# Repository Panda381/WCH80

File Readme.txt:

WCH80 BabyPC - mini-computer with CH32V002, ZX80 clone
======================================================
Version 1.0, September 2025

Copyright (c) 2025 Miroslav Nemecek

Panda38@seznam.cz
hardyplotter2@gmail.com
https://github.com/Panda381/WCH80
https://www.breatharian.eu/hw/wch80/index_en.html

This project is part of the CH32LibSDK library:
https://github.com/Panda381/CH32LibSDK
https://www.breatharian.eu/hw/ch32libsdk/index_en.html

License
-------
All of my software creations are distributed under the Unlicense
https://spdx.org/licenses/Unlicense.html,
and my hardware creations under the CC0 license
https://creativecommons.org/publicdomain/zero/1.0/legalcode.en.
You are free to use, modify, and distribute them for any purpose without having
to credit me as the author. The exception is content derived from third-party
sources. These third-party components are not covered by my Unlicense or CC0
licenses, but rather by the original license terms of their authors. These
components are marked in the code, and when using them, you must comply with
the terms of the original licenses.

Folders
-------
!Babypc ... binaries - firmware of CPU1 and CPU2, BASIC80, games
_devices ... source codes of WCH80 device library
Babypc ... source codes of firmware of CPU1 and CPU2, BASIC80, games

Description
-----------
The WCH80 BabyPC is an inexpensive mini-computer with two CH32V002
processors, created based on the ZX80 computer. It is not an emulator;
the computer does not emulate the ZX80 computer's ROM, nor does it emulate Z80
machine instructions. It was created as a completely independent computer with
the BASIC80 programming language and VGA monitor output, only replicating the
ZX80's functionality as closely as possible. It uses a CH32V002A4M6 processor,
which, thanks to its large 1.27 mm pin pitch, is suitable for easy soldering
even for novice designers. Together with other THT components, the WCH80 is
particularly suitable as a kit for novice designers. The built-in BASIC80
programming language is used to familiarize users with computer programming and
to try out how programmers programmed in the 1980s.

The computer does not contain a storage medium for saving programs. Your own
programs can be saved directly to the processor's flash memory. There are 14
memory slots available, i.e. 14 places to store your own programs, numbered 0
to 13. Slot 0 is located in the main CPU1 processor. When stored in slot 0,
data variables are also stored along with the program (more precisely, only the
first half of the memory with variables). Slot 0 is automatically loaded into
the program memory when the computer is turned on. Memory slots 1 to 13 are
located in the second processor, CPU2. All slots allow the entire memory with
the program to be stored, except for the last slot 13, which is only half the
size.

After initial programming, the processors contain 28 sample programs and games
written in BASIC80. Once the processors have been programmed, the programmer is
no longer needed, but it can be useful if you want to back up the contents of
the processors to a PC or if you want to change program versions. Using slot 0,
programs can also be transferred between the processors' memory backups by
copying between the CPU1 and CPU2 processors.

In addition to the BASIC80 firmware, games and programs written in C can also
be uploaded to the computer using a programmer. There are 25 sample games
available. The games can be found in the CH32LibSDK library. However, it is
important to remember that reprogramming the CPU1 processor will also overwrite
the contents of slot 0. The contents of slots 1 to 13 in CPU2 will not change
when games are loaded. For games in C code, the following keys are usually used
for control: 8, F=right, 7, E=up, 5, S=left, 6, D=down, A, space=action, B,
NEW LINE=alternative action, X, P=info, Y, 0=back.

Differences between WCH80 and ZX80:

- Image output to a VGA monitor (instead of a TV).
- Fixed size of memory buffers: 768 B for the image buffer, 1 KB for the
  program, 1 KB for data variables (instead of 1 KB for everything).
- Z80 machine code and the USR() user function are not supported.
- Numerical calculations and variables are 32-bit (instead of 16-bit).
- All variable types can use long names, including the dot character (in ZX80,
  long names are only for numerical variables).
- Program storage in flash memory slots (instead of on tape).
- Sound output for playing tones and melodies.
- Added functions MEMORY, DATA, READ, WAIT, BEEP, INKEY$.
- The program line number can be in the range 1 to 65534.
- Different functionality of the POKE and PEEK commands.
- Percent sign % instead of pound sign in the image generator.
- I2C interface available, but only from programs in C code, not available
  from BASIC80.
- No expansion connector for external modules available.

Wiring diagram
--------------
The WCH80 contains two CH32V002A4M6 processors. The first processor, CPU1, is
the main processor. It contains BASIC80 or programs and games. If it contains
BASIC80, the last 1.5 KB of flash memory is reserved for storing the program
and data, as memory slot 0. The processor is controlled by a 25 MHz crystal.
The crystal (and the corresponding capacitors) may not be necessary to use - in
that case, the processor will use an internal HSI oscillator, which, however,
may not have sufficient stability - this will manifest itself as a slight
shaking of the video lines in the image.

The second processor, CPU2, is used to control the key matrix and to store
programs, such as memory slots 1 to 13. The processors communicate with each
other via the USART interface. After programming the CPU2 processor, it is
necessary to reset the computer by disconnecting the power supply so that the
processors can establish a connection with each other. The CPU1 processor is
programmed via the SWIO1 connector, and the CPU2 processor via the SWIO2
connector. After the initial programming of the processors, the sample program
in slot 0 can be used to check functionality. After turning on the power, press
the R (=RUN) and NEW LINE buttons. This can be done even without a monitor
connected. The audio output should emit a beep at 1-second intervals.

Construction
------------
In the prototype, I used a single-sided printed circuit board manufactured
using a photo process with dimensions of 10x7.5 cm (limitation of the free
version of Eagle), so it is not certain whether the design is also ready for
custom production of printed circuit boards. I used THT components to make
assembly easier, including a large USB-B connector. Instead of the top side of
the printed circuit board, I used wires. When programming processors, pay
attention to the correct pin assignment. I used a socket for the crystal -
just so I could test the functionality without the crystal. Micro switches
with low actuation force are used as buttons.

I printed the button labels on an inkjet printer on plain paper, covered both
sides with transparent adhesive tape, and cut out the holes for the buttons
with a 4 mm leather punch. For the final design, you will probably use
a printed circuit board with holes and button labels as the top cover.

Description of the WCH80 BASIC80 language
-----------------------------------------
WCH80 BASIC80 is almost identical to ZX80 BASIC, except for a few differences.
Program editing takes place in RAM memory. The maximum program size is 1 KB.
Data variables are stored in a separate buffer in RAM memory, also with a size
of 1 KB. The screen buffer has a fixed size of 768 bytes (24 lines of text
with 32 characters each).

The program line number can be in the range of 1 to 65534. Calculations are
performed with 32-bit integers in the range -2147483648 to +2147483647 (note:
the constant -2147483648 cannot be entered numerically, but is used in
calculations). Variable names of all types can be between 1 and 63 characters
long. The first character must be a letter. Subsequent characters can be
letters, digits, and periods. A period can be used as a word separator.
Variables can be of the following types:

- integer variable
- text variable with a $ sign after the name
- numeric array with a parenthesis '(' after the name, the array index can be
  max. 255
- The result of comparison operators is the number 0 (= condition not met) or
  -1 (= condition met, in HEX code this is the number 0xFFFFFFFF). The
  operators AND, OR, and NOT can be used as logical operators or as bitwise
  operators.

Keys for editing the program:

- EDIT ... (Shift+NEW LINE) load the selected line into the editor
- LEFT ... (Shift+5) move the cursor to the left
- DOWN ... (Shift+6) move the cursor to the next line
- UP ... (Shift+7) move the cursor to the previous line
- RIGHT ... (Shift+8) move the cursor to the right
- HOME ... (Shift+9) move the cursor to the beginning of the program
- RUBOUT ... (Shift+0) delete the character before the cursor
- NEW LINE ... end editing, execute the command, or save the line to the
        program (if it contains a line number at the beginning)

Operations, sorted by highest priority:

- ** ... (10) (Shift+H) power
- - ... (9) (Shift+J) negation (unary minus)
- * ... (8) (Shift+P) multiplication
- / ... (7) (Shift+V) division (integer result)
- + ... (6) (Shift+K) sum
- - ... (6) (Shift+J) difference
- = ... (5) (Shift+L) comparison of numbers and texts for equality
- < ... (5) (Shift+N) comparison of numbers and texts for lesser than
- > ... (5) (Shift+M) comparison of numbers and texts for greater
- NOT ... (4) (Shift+1) bitwise and logical inversion (unary operation)
- AND ... (3) (Shift+2) bitwise and logical product
- OR ... (2) (Shift+B) bitwise and logical sum

Beware that multiplication has higher priority than division.

Commands - can only be at the beginning of a line or after the THEN command,
and are invoked by pressing the letter:

LIST ... (A) Lists the program from the specified line. Without specifying
             a line number, lists from the beginning.
BEEP ... (B) Plays a tone. The first numerical parameter is the tone frequency
             in multiples of 0.01Hz. The number 0 ensures a delay. The second
             parameter is the tone length in milliseconds. For example,
             BEEP 100000,1000 plays a tone with a frequency of 1 kHz and a
             length of 1 second.
CLS ... (C) Clears the screen.
DIM ... (D) Array declaration. This is followed by the name of the variable and
            the maximum index 0 to 255 in parentheses. For example, entering
            DIM A(255) declares an array with 256 items, index 0 to 255.
SAVE ... (E) Saves the program to a slot in flash memory. This is followed by
             the slot number 0 to 13. If no slot number is entered, slot 0 is
             used. Slot 0 is in the main CPU1 processor. Slots 1 to 13 are in
             the second CPU2 processor. All slots are 1 KB in size (i.e., they
             can hold the entire program), except for slot 13, which is only
             512 bytes in size. When a program is saved to slot 0, the data
             variables are also saved at the same time - but only up to a buffer
             size of 512 bytes. Data is not saved for other slots. When the
             computer is started, the program from slot 0 is automatically
             loaded into the program memory.
FOR ... (F) Start of the cycle. This is followed by the name of the variable,
            an equal sign, and the initial value. The TO command is followed by
            the end value. After each pass through the cycle, the NEXT command
            increases the value of the variable by 1 until it exceeds the end
            value.
GOTO ... (G) Jump to the specified line number. An expression can also be
             specified to jump to different locations. By entering it directly
             (not in the program), the program can be run without deleting
             variables, thus continuing the stopped program.
POKE ... (H) Writes data to system registers. This is followed by an address
             and a value. Unlike ZX80 and other BASIC languages, this is not
             a memory address, but a register number. The address has the
             following meaning: 0 to 767: image memory, -1: image frame counter
             (can be used as a timer with a frequency of 60 Hz), -2: SEED
             register of the random number generator, -3: timer incremented by
             20 ns (i.e., frequency of 50 MHz), -4: position on the X screen
             (0 to 32), -5 line on the Y screen (0 to 23).
INPUT ... (I) User input. Followed by the name of the target numeric or text
              variable.
RANDOMISE ... (J) Initialization of the random number generator with the
             specified number. Entering 0 or omitting the parameter performs
             automatic initialization to a random value.
RETURN ... (K) Return from the procedure.
LET ... (L) Setting the content of a variable. Followed by the name of the
            variable, an equal sign, and an expression.
MEMORY ... (M) Displays RAM memory usage. Lists 4 values: occupied program
               memory, free program memory, occupied data memory, and free data
               memory.
NEXT ... (N) Continues the cycle for the specified variable. Followed by the
             name of the numeric variable. The command increments the variable
             and, if the target value has not been reached, jumps to the
             corresponding FOR function.
LOAD ... (O) Loads the program from a slot in the flash memory. This is
             followed by the slot number 0 to 13. If no slot number is
             specified, slot 0 is used. Slot number 0 is in the main CPU1
             processor. Slots 1 to 13 are in the second CPU2 processor. All
             slots are 1 KB in size (i.e., they can hold the entire program),
             except for slot 13, which is only 512 bytes in size. When loading
             a program from slot 0, the data variables are also loaded at the
             same time, but only up to a buffer size of 512 bytes. The data for
             other slots is not restored. When the computer is started, the
             program and data from slot 0 are automatically loaded into the
             program memory.
PRINT ... (P) Prints the value of a numerical expression or text. The ';'
             character ensures continuation without a space, the ',' character
             indents after 8-character tab positions. If neither the ';' nor
             the ',' character is specified at the end of the PRINT command,
             new line is inserted.
NEW ... (Q) Deletes the program and variables.
RUN ... (R) Runs the program from the specified line. If no line number is
            specified, the program starts from the beginning. At the same time,
            it deletes the variables.
STOP ... (S) Stops the program. You can continue with the CONTINUE command.
CONTINUE ... (T) Continues the program from where it was interrupted by the
             STOP command.
IF ... (U) Condition. THEN is followed by a command executed if the condition
           or expression is true. The expression is valid (True) if it is not
           zero.
GOSUB .. (V) Jump to a procedure. The procedure returns with the RETURN command
             to the line following GOSUB.
WAIT ... (W) Waits for the specified time in milliseconds.
CLEAR ... (X) Clears variables.
REM ... (Y) Comment.
DATA ... (Z) List of data. Numeric constants or numeric expressions separated
             by commas follow. Text cannot be used. Data is read from the list
             using the READ command.

Special commands:

- " ... (Shift+Y) Quotation mark, indicates the beginning and end of text.
- THEN ... (Shift+3) Part of the IF condition, indicates a command executed
         when the condition is met.
- TO ... (Shift+4) Part of the FOR loop, indicates the end value of
         a variable.
- ; ... (Shift+Z) Part of the PRINT command, continues printing from the
         last position.
- , ... (Shift+.) Part of the PRINT command, continues printing from the
         tab position.
- ( ) ... (Shift+I, Shift+O) Parentheses.

Functions - functions must be written in text form, they do not have keyboard
shortcuts:

PEEK ... Reads the contents of the system register. The address follows in
         parentheses. Unlike ZX80 and other BASIC languages, this is not a
         memory address, but a register number. The address has the following
         meaning: 0 to 767: image memory, 3584 to 4095: fonts, -1: image frame
         counter (can be used as a timer with a frequency of 60 Hz), -2: SEED
         register of the random number generator, -3: timer incremented by
         20 ns (i.e., frequency 50 MHz), -4: position on the screen X (0 to
         32), -5 row on the screen Y (0 to 23).
CHR$ ... Conversion of a character number to a text character.
CODE ... Conversion of a text character (first character of text) to a numeric
         code.
RND ... Random number generator, generates a number from 1 to the specified
        maximum number. Returns 1 for 0 and negative numbers.
TL$ ... Returns text without the first character.
STR$ ... Conversion of a number to text.
ABS ... Absolute value of a number.
INKEY$ ... Returns a character from the keyboard as text. Empty text means that
         no key was pressed.
READ ... Returns data from the DATA table. The command is used differently than
         is usual in other BASIC languages. It is not used as a command with a
         variable, but is used in a numeric expression as a function (without
         parentheses). Returns the value from the expression in the DATA table,
         according to the current data read pointer. Expressions can also
         contain variables, so the data may vary during the program. When the
         pointer reaches the end of the program, it automatically resets to the
         beginning.

Sample programs
---------------
Sample programs are stored in flash memory in memory slots 0 to 13 until they
are overwritten by a user program. The contents of the programs can be found in
the Programs.txt file.

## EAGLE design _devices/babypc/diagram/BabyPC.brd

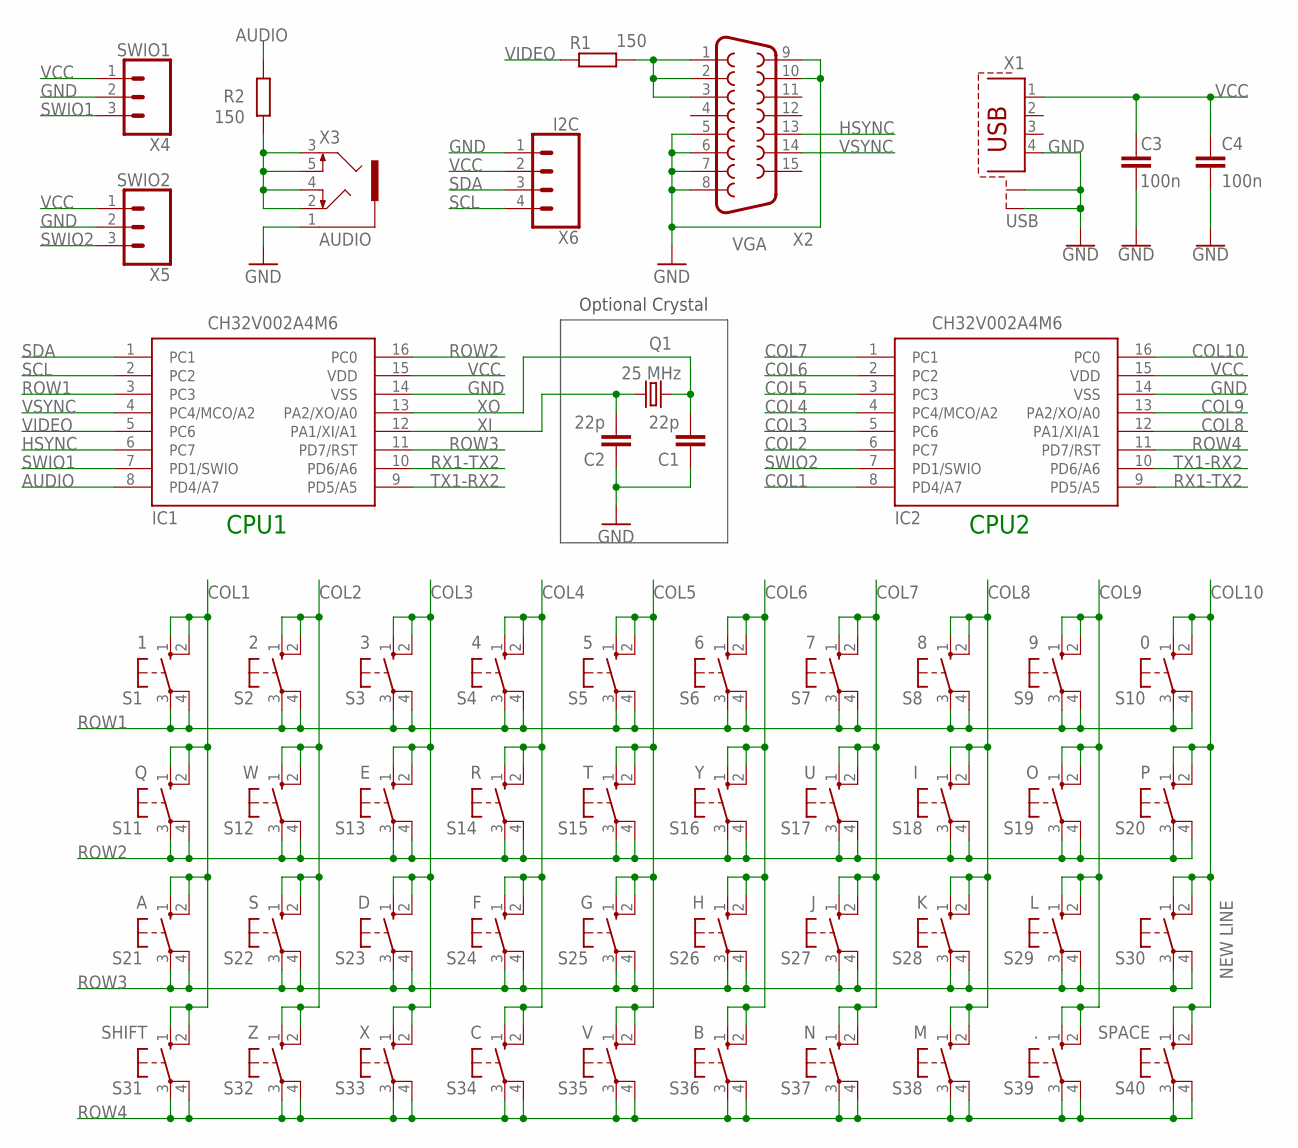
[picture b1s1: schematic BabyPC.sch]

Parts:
C1, C2: 22p; C050-024X044
C3, C4: 100n; C050-024X044
IC1, IC2: CH32V002A4M6; SOP16
Q1: 25 MHz; HC49U-V
R1, R2: 150; 0204/7
S1: 1; B3F-10XX
S2: 2; B3F-10XX
S3: 3; B3F-10XX
S4: 4; B3F-10XX
S5: 5; B3F-10XX
S6: 6; B3F-10XX
S7: 7; B3F-10XX
S8: 8; B3F-10XX
S9: 9; B3F-10XX
S10: 0; B3F-10XX
S11: Q; B3F-10XX
S12: W; B3F-10XX
S13: E; B3F-10XX
S14: R; B3F-10XX
S15: T; B3F-10XX
S16: Y; B3F-10XX
S17: U; B3F-10XX
S18: I; B3F-10XX
S19: O; B3F-10XX
S20: P; B3F-10XX
S21: A; B3F-10XX
S22: S; B3F-10XX
S23: D; B3F-10XX
S24: F; B3F-10XX
S25: G; B3F-10XX
S26: H; B3F-10XX
S27: J; B3F-10XX
S28: K; B3F-10XX
S29: L; B3F-10XX
S30: NEW LINE; B3F-10XX
S31: SHIFT; B3F-10XX
S32: Z; B3F-10XX
S33: X; B3F-10XX
S34: C; B3F-10XX
S35: V; B3F-10XX
S36: B; B3F-10XX
S37: N; B3F-10XX
S38: M; B3F-10XX
S39: .; B3F-10XX
S40: SPACE; B3F-10XX
X1: USB; PN61729-S
X2: VGA; HDF15H
X3: AUDIO; 1503_09
X4: SWIO1; 1X03_LONGPADS
X5: SWIO2; 1X03_LONGPADS
X6: I2C; 1X04_LONGPADS

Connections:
AUDIO: IC1.8 (PD4/A7), R2.2
COL1: IC2.8 (PD4/A7), S1.1 (S), S1.2 (S1), S11.1 (S), S11.2 (S1), S21.1 (S), S21.2 (S1), S31.1 (S), S31.2 (S1)
COL2: IC2.6 (PC7), S2.1 (S), S2.2 (S1), S12.1 (S), S12.2 (S1), S22.1 (S), S22.2 (S1), S32.1 (S), S32.2 (S1)
COL3: IC2.5 (PC6), S3.1 (S), S3.2 (S1), S13.1 (S), S13.2 (S1), S23.1 (S), S23.2 (S1), S33.1 (S), S33.2 (S1)
COL4: IC2.4 (PC4/MCO/A2), S4.1 (S), S4.2 (S1), S14.1 (S), S14.2 (S1), S24.1 (S), S24.2 (S1), S34.1 (S), S34.2 (S1)
COL5: IC2.3 (PC3), S5.1 (S), S5.2 (S1), S15.1 (S), S15.2 (S1), S25.1 (S), S25.2 (S1), S35.1 (S), S35.2 (S1)
COL6: IC2.2 (PC2), S6.1 (S), S6.2 (S1), S16.1 (S), S16.2 (S1), S26.1 (S), S26.2 (S1), S36.1 (S), S36.2 (S1)
COL7: IC2.1 (PC1), S7.1 (S), S7.2 (S1), S17.1 (S), S17.2 (S1), S27.1 (S), S27.2 (S1), S37.1 (S), S37.2 (S1)
COL8: IC2.12 (PA1/XI/A1), S8.1 (S), S8.2 (S1), S18.1 (S), S18.2 (S1), S28.1 (S), S28.2 (S1), S38.1 (S), S38.2 (S1)
COL9: IC2.13 (PA2/XO/A0), S9.1 (S), S9.2 (S1), S19.1 (S), S19.2 (S1), S29.1 (S), S29.2 (S1), S39.1 (S), S39.2 (S1)
COL10: IC2.16 (PC0), S10.1 (S), S10.2 (S1), S20.1 (S), S20.2 (S1), S30.1 (S), S30.2 (S1), S40.1 (S), S40.2 (S1)
GND: C1.1, C2.1, C3.1, C4.2, IC1.14 (VSS), IC2.14 (VSS), X1.4, X1.S1, X1.S2, X2.5, X2.6, X2.7, X2.8, X2.9, X2.10, X3.1, X4.2, X5.2, X6.1
HSYNC: IC1.6 (PC7), X2.13
unnamed: R2.1, X3.2, X3.3, X3.4, X3.5
unnamed: R1.2, X2.1, X2.2, X2.3
ROW1: IC1.3 (PC3), S1.3, S1.4 (P1), S2.3, S2.4 (P1), S3.3, S3.4 (P1), S4.3, S4.4 (P1), S5.3, S5.4 (P1), S6.3, S6.4 (P1), S7.3, S7.4 (P1), S8.3, S8.4 (P1), S9.3, S9.4 (P1), S10.3, S10.4 (P1)
ROW2: IC1.16 (PC0), S11.3, S11.4 (P1), S12.3, S12.4 (P1), S13.3, S13.4 (P1), S14.3, S14.4 (P1), S15.3, S15.4 (P1), S16.3, S16.4 (P1), S17.3, S17.4 (P1), S18.3, S18.4 (P1), S19.3, S19.4 (P1), S20.3, S20.4 (P1)
ROW3: IC1.11 (PD7/RST), S21.3, S21.4 (P1), S22.3, S22.4 (P1), S23.3, S23.4 (P1), S24.3, S24.4 (P1), S25.3, S25.4 (P1), S26.3, S26.4 (P1), S27.3, S27.4 (P1), S28.3, S28.4 (P1), S29.3, S29.4 (P1), S30.3, S30.4 (P1)
ROW4: IC2.11 (PD7/RST), S31.3, S31.4 (P1), S32.3, S32.4 (P1), S33.3, S33.4 (P1), S34.3, S34.4 (P1), S35.3, S35.4 (P1), S36.3, S36.4 (P1), S37.3, S37.4 (P1), S38.3, S38.4 (P1), S39.3, S39.4 (P1), S40.3, S40.4 (P1)
RX1-TX2: IC1.10 (PD6/A6), IC2.9 (PD5/A5)
SCL: IC1.2 (PC2), X6.4
SDA: IC1.1 (PC1), X6.3
SWIO1: IC1.7 (PD1/SWIO), X4.3
SWIO2: IC2.7 (PD1/SWIO), X5.3
TX1-RX2: IC1.9 (PD5/A5), IC2.10 (PD6/A6)
VCC: C3.2, C4.1, IC1.15 (VDD), IC2.15 (VDD), X1.1, X4.1, X5.1, X6.2
VIDEO: IC1.5 (PC6), R1.1
VSYNC: IC1.4 (PC4/MCO/A2), X2.14
XI: C2.2, IC1.12 (PA1/XI/A1), Q1.2
XO: C1.2, IC1.13 (PA2/XO/A0), Q1.1

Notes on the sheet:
Optional Crystal
CPU1
CPU2

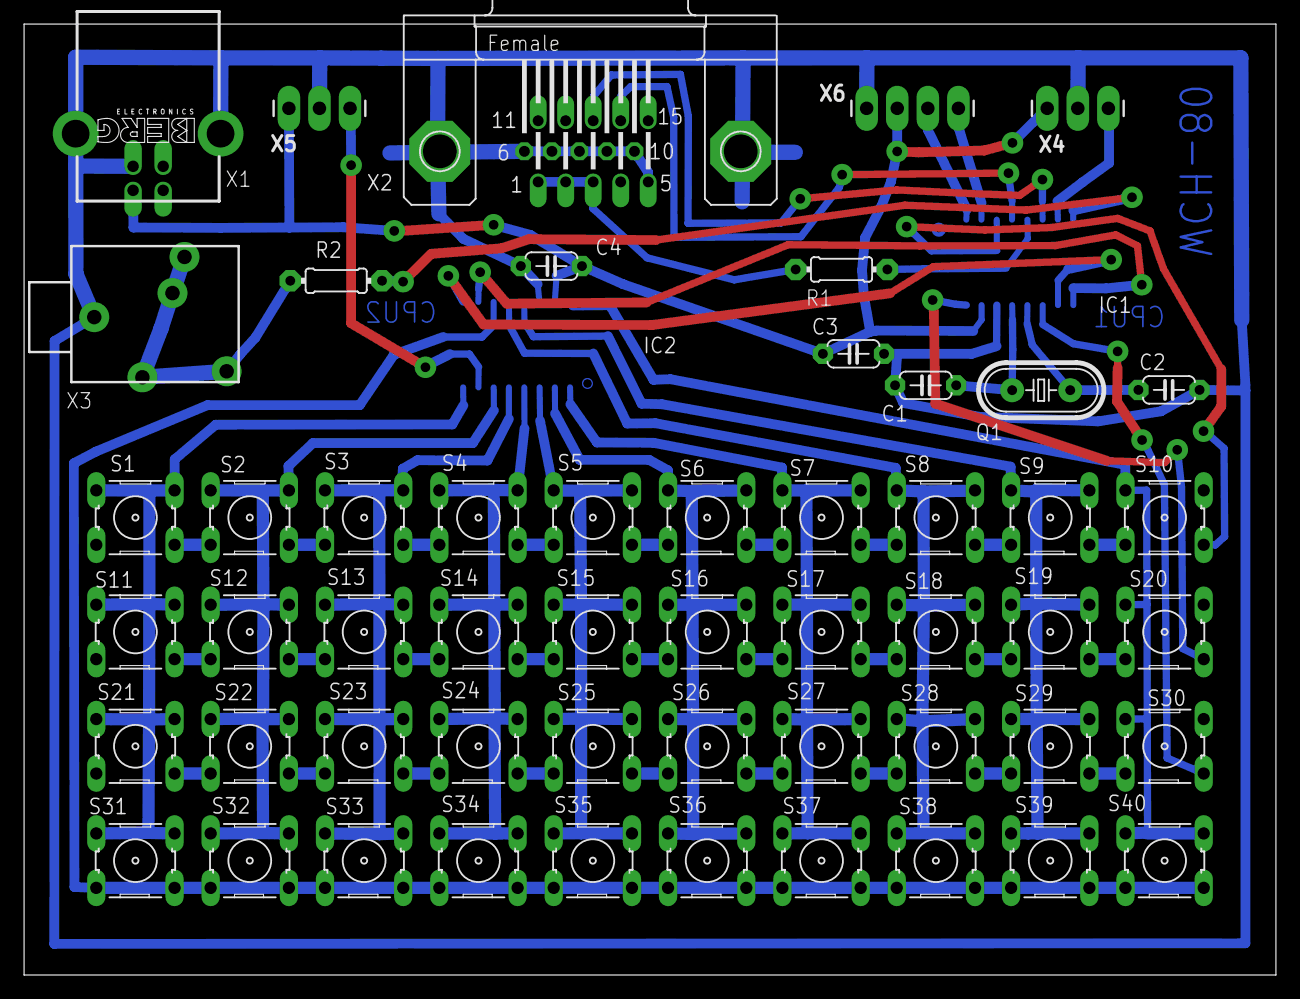
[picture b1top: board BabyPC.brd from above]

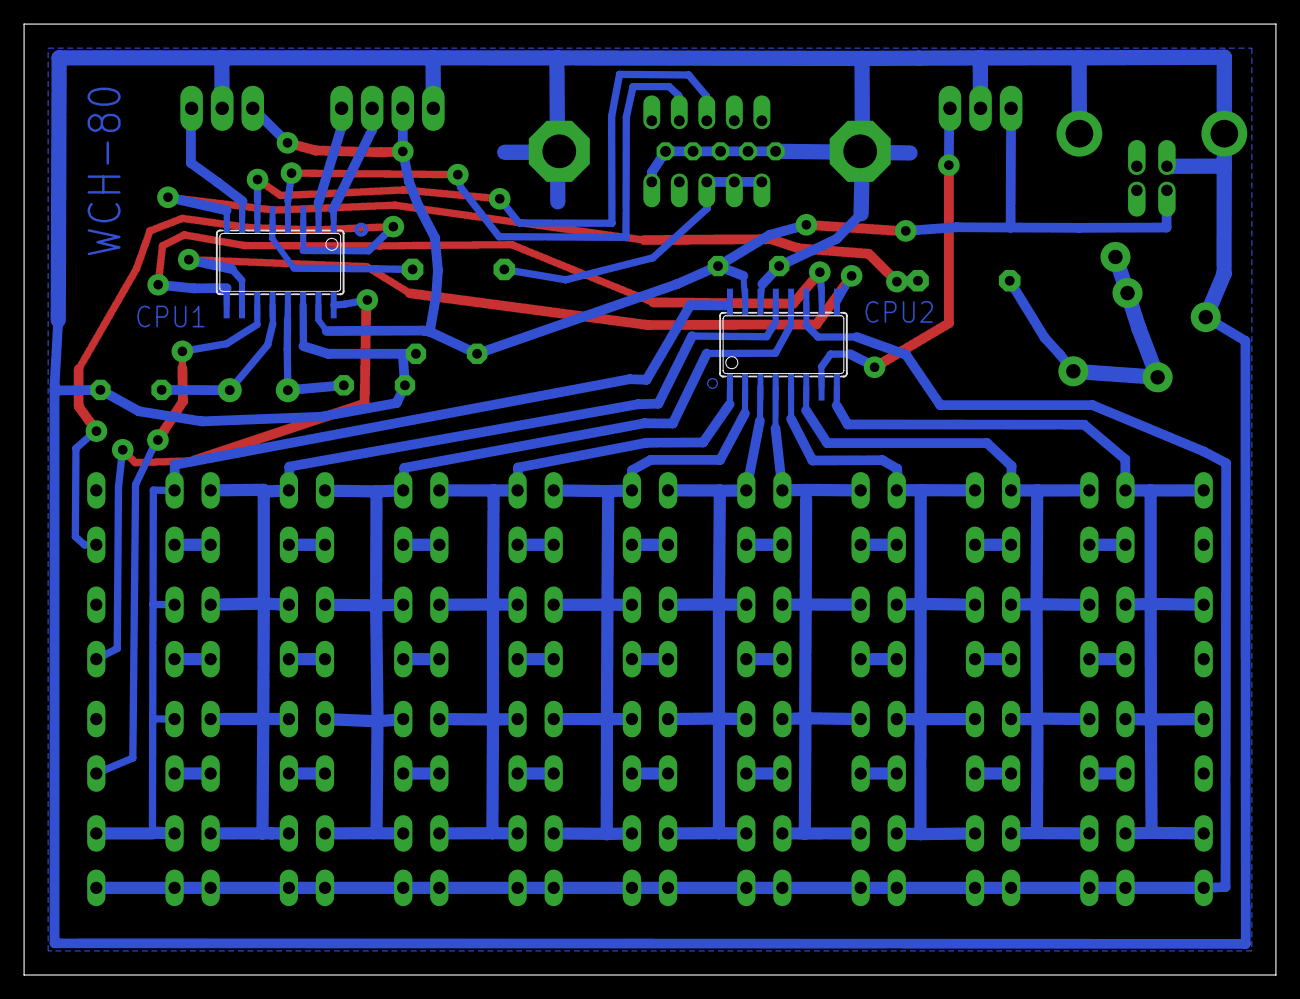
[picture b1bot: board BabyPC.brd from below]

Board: 2 copper layers, 104.0 x 79.0 mm, 55 parts (2 on the bottom side), 30 nets.

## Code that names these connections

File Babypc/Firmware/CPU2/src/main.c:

// PC1: COL7
// PC2: COL6
// PC3: COL5
// PC4: COL4
// PC6: COL3
// PC7: COL2
// PD4: COL1
// PD5: USART1_TX mapping 0, RX1-TX2 (send from CPU2 to CPU1, this is CPU2)
// PD6: USART1_RX mapping 0, TX1-RX2 (send from CPU1 to CPU2, this is CPU2)
// PD7: ROW4 (RST)
// PA1: COL8
// PA2: COL9
// PC0: COL10

// Input from the buttons is handled during the VGA rendering service,
// during back porch vertical scanlines (33 scanlines).
// Whole line = 31.8 us. 10us to transfer 1 byte.

// start of scanline 1:
//  time 0us: CPU1 start sending CPU_CMD_ROW4x
//  time 10us: CPU2 received CPU_CMD_ROW4x
//  time 12us: CPU2 start sending response byte 1
//  time 22us: CPU1 has byte 1 ready in buffer
// start of scanline 2:
//  time 32us: CPU1 received byte 1, CPU1 processed byte 1
//  time 43us: CPU2 start sending response byte 2
//  time 53us: CPU1 has byte 2 ready in buffer
// start of scanline 3:
//  time 64us: CPU1 start sending CPU_CMD_ROW4x
//  time 64us: CPU1 received byte 2, CPU1 processed byte 2

#define CPU_SEND_WAIT	31		// wait delay in [us] after sending first column byte

// USART communication divider (baudrate = HCLK/div, HCLK=48000000, div=min. 16; 48 at 48MHz -> 1MBaud, 1 byte = 10us)
#define CPU_UART_DIV	HCLK_PER_US	// USART CPU baudrate divider (baudrate = HCLK/div, HCLK=48000000, div=min. 16)

// commands from CPU1 to CPU2
#define CPU_CMD_SYNC	0x16		// sync - echo CPU_STATE_SYNC back, and set ROW4 to 1
#define CPU_CMD_ROW41	0x17		// return columns in 2 bytes (in bits 0..4) and set ROW4 to 1
#define CPU_CMD_ROW40	0x18		// return columns in 2 bytes (in bits 0..4) and set ROW4 to 0

#define CPU_CMD_LOAD1	0x20		// load program from slot 1
#define CPU_CMD_LOAD2	0x21		// load program from slot 2
#define CPU_CMD_LOAD3	0x22		// load program from slot 3
#define CPU_CMD_LOAD4	0x23		// load program from slot 4
#define CPU_CMD_LOAD5	0x24		// load program from slot 5
#define CPU_CMD_LOAD6	0x25		// load program from slot 6
#define CPU_CMD_LOAD7	0x26		// load program from slot 7
#define CPU_CMD_LOAD8	0x27		// load program from slot 8
#define CPU_CMD_LOAD9	0x28		// load program from slot 9
#define CPU_CMD_LOAD10	0x29		// load program from slot 10
#define CPU_CMD_LOAD11	0x2A		// load program from slot 11
#define CPU_CMD_LOAD12	0x2B		// load program from slot 12
#define CPU_CMD_LOAD13	0x2C		// load program from slot 13

#define CPU_CMD_SAVE1	0x30		// save program to slot 1
#define CPU_CMD_SAVE2	0x31		// save program to slot 2
#define CPU_CMD_SAVE3	0x32		// save program to slot 3
#define CPU_CMD_SAVE4	0x33		// save program to slot 4
#define CPU_CMD_SAVE5	0x34		// save program to slot 5
#define CPU_CMD_SAVE6	0x35		// save program to slot 6
#define CPU_CMD_SAVE7	0x36		// save program to slot 7
#define CPU_CMD_SAVE8	0x37		// save program to slot 8
#define CPU_CMD_SAVE9	0x38		// save program to slot 9
#define CPU_CMD_SAVE10	0x39		// save program to slot 10
#define CPU_CMD_SAVE11	0x3A		// save program to slot 11
#define CPU_CMD_SAVE12	0x3B		// save program to slot 12
#define CPU_CMD_SAVE13	0x3C		// save program to slot 13

// state from CPU2 to CPU1
#define CPU_STATE_SYNC	0x15		// sync - echo back after CPU_CMD_SYNC

#include "../include.h"

// receive slot
sSlot Slot0;

// check free send byte to other CPU
Bool CPU_SendReady()
{
	return USART1_TxEmpty();
}

// send byte to other CPU
void CPU_Send(u8 data)
{
	USART1_SendChar(data);
}

// check received byte from other CPU
Bool CPU_RecvReady()
{
	return USART1_RxReady();
}

// receive byte from other CPU
u8 CPU_Recv()
{
	return USART1_RecvChar();
}

// remapping table of bits of PC port (table size: 512 bytes)
//  0 -> 9 (PC0 -> COL10)
//  1 -> 6 (PC1 -> COL7)
//  2 -> 5 (PC2 -> COL6)
//  3 -> 4 (PC3 -> COL5)
//  4 -> 3 (PC4 -> COL4)
//  6 -> 2 (PC6 -> COL3)
//  7 -> 1 (PC7 -> COL2)
u16 PortCRemap[256];

int main(void)
{
	u8 ch, ra, rc, rd;
	u32 r;
	u16 kk;
	int i;

	// prepare remapping table
// remapping table of bits of PC port (table size: 512 bytes)
//  0 -> 9 (PC0 -> COL10)
//  1 -> 6 (PC1 -> COL7)
//  2 -> 5 (PC2 -> COL6)
//  3 -> 4 (PC3 -> COL5)
//  4 -> 3 (PC4 -> COL4)
//  6 -> 2 (PC6 -> COL3)
//  7 -> 1 (PC7 -> COL2)
	for (i = 0; i < 256; i++)
	{
		kk = 0;
		if ((i & B0) == 0) kk |= B9;
		if ((i & B1) == 0) kk |= B6;
		if ((i & B2) == 0) kk |= B5;
		if ((i & B3) == 0) kk |= B4;
		if ((i & B4) == 0) kk |= B3;
		if ((i & B6) == 0) kk |= B2;
		if ((i & B7) == 0) kk |= B1;
		PortCRemap[i] = kk;
	}

	// initialize port clock
	RCC_AFIClkEnable();
	RCC_PAClkEnable();
	RCC_PCClkEnable();
	RCC_PDClkEnable();

	// trim HSI oscillator to 24MHz
	RCC_HSITrim(16);

	// switch PD7 to GPIO mode, if not already set
	if (((OB->USER >> 3) & 3) != 3)
	{
		OB_t ob;
		Flash_OBRead(&ob);	// read option bytes
		ob.USER |= B3|B4;	// disable RESET function
		Flash_OBWrite(&ob);	// write new option bytes
	}

	// Remap PA1 & PA2 pins to OSC_IN & OSC_OUT (default 0)
	// 0 ... pins PA1 & PA2 are used as GPIO ports
	GPIO_Remap_PA1PA2(0);

	// setup column pins to IN_PU pull-up
	GPIO_Mode(PC1, GPIO_MODE_IN_PU);	// COL7, pin 1
	GPIO_Mode(PC2, GPIO_MODE_IN_PU);	// COL6, pin 2
	GPIO_Mode(PC3, GPIO_MODE_IN_PU);	// COL5, pin 3
	GPIO_Mode(PC4, GPIO_MODE_IN_PU);	// COL4, pin 4
	GPIO_Mode(PC6, GPIO_MODE_IN_PU);	// COL3, pin 5
	GPIO_Mode(PC7, GPIO_MODE_IN_PU);	// COL2, pin 6
	GPIO_Mode(PD4, GPIO_MODE_IN_PU);	// COL1, pin 8
	GPIO_Mode(PA1, GPIO_MODE_IN_PU);	// COL8, pin 12
	GPIO_Mode(PA2, GPIO_MODE_IN_PU);	// COL9, pin 13
	GPIO_Mode(PC0, GPIO_MODE_IN_PU);	// COL10, pin 16

	// setup row4
	GPIO_Out1(PD7);		// ROW4
	GPIO_Mode(PD7, GPIO_MODE_OD);	// ROW4

	// setup USART1 mapping 0, to communicate with CPU1
	// 0 ... PD5:TX, PD6:RX, PD3:CTS, PC2:RTS
// PD5: USART1_TX mapping 0, TX1-RX2 (send from CPU1 to CPU2, this is CPU1)
// PD6: USART1_RX mapping 0, RX1-TX2 (send from CPU2 to CPU1, this is CPU1)
	GPIO_Remap_USART1(0);
	USART1_Init((RCC_GetFreq(CLK_HCLK) + CPU_UART_DIV/2)/CPU_UART_DIV,
		USART_WORDLEN_8, USART_PARITY_NONE, USART_STOP_1);
	GPIO_Mode(PD5, GPIO_MODE_AF);		// TX
	GPIO_Mode(PD6, GPIO_MODE_IN);		// RX

	while(True)
	{
		if (CPU_RecvReady() && CPU_SendReady())
		{
			ch = CPU_Recv();
			switch (ch)
			{
			// sync - echo CPU_STATE_SYNC back
			case CPU_CMD_SYNC:
				CPU_Send(CPU_STATE_SYNC);
				GPIO_Out1(PD7);		// disable ROW4
				break;

			// return columns in 2 bytes (in bits 0..4) and set ROW4 to 1
			case CPU_CMD_ROW41:
			// return columns in 2 bytes (in bits 0..4) and set ROW4 to 0
			case CPU_CMD_ROW40:

				// read columns
				ra = GPIOA_InAll();
				rc = GPIOC_InAll();
				rd = GPIOD_InAll();
				i = PortCRemap[rc];
				if ((rd & B4) == 0) i |= B0;
				i |= ((~ra) & (B1 | B2)) << 6;

				// send columns
				CPU_Send((u8)(i & 0x1f));
				WaitUs(CPU_SEND_WAIT);
				CPU_Send((u8)(i >> 5));

				// set ROW4
				if (ch == CPU_CMD_ROW41)
					GPIO_Out1(PD7);		// disable ROW4
				else
					GPIO_Out0(PD7);		// enable ROW4
				break;

			// load from slot
			case CPU_CMD_LOAD1:
			case CPU_CMD_LOAD2:
			case CPU_CMD_LOAD3:
			case CPU_CMD_LOAD4:
			case CPU_CMD_LOAD5:
			case CPU_CMD_LOAD6:
			case CPU_CMD_LOAD7:
			case CPU_CMD_LOAD8:
			case CPU_CMD_LOAD9:
			case CPU_CMD_LOAD10:
			case CPU_CMD_LOAD11:
			case CPU_CMD_LOAD12:
				{
					int inx = ch - CPU_CMD_LOAD1;
					const sSlot* s = &Slots[inx];
					for (i = 0; i < SLOTNUM; i++)
					{
						while (!CPU_SendReady()) {}
						CPU_Send(s->data[i]);
						WaitUs(CPU_SEND_WAIT*2); // CPU1 can be interrupted by HSYNC
					}
				}
				break;

			case CPU_CMD_LOAD13:
				{
					const u8* s = Slot13;
					for (i = 0; i < SLOT13NUM; i++)
					{
						while (!CPU_SendReady()) {}
						CPU_Send(s[i]);
						WaitUs(CPU_SEND_WAIT*2); // CPU1 can be interrupted by HSYNC
					}

					for (; i < SLOTNUM; i++)
					{
						while (!CPU_SendReady()) {}
						CPU_Send(0xff);
						WaitUs(CPU_SEND_WAIT*2); // CPU1 can be interrupted by HSYNC
					}
				}
				break;

			// save to slot
			case CPU_CMD_SAVE1:
			case CPU_CMD_SAVE2:
			case CPU_CMD_SAVE3:
			case CPU_CMD_SAVE4:
			case CPU_CMD_SAVE5:
			case CPU_CMD_SAVE6:
			case CPU_CMD_SAVE7:
			case CPU_CMD_SAVE8:
			case CPU_CMD_SAVE9:
			case CPU_CMD_SAVE10:
			case CPU_CMD_SAVE11:
			case CPU_CMD_SAVE12:
			case CPU_CMD_SAVE13:
				{
					// receive data
					sSlot* s0 = &Slot0;
					for (i = 0; i < SLOTNUM; i++)
					{
						while (!CPU_RecvReady()) {}
						s0->data[i] = CPU_Recv();
					}

					// prepare slot address and size
					const u8* s;
					int n;
					if (ch == CPU_CMD_SAVE13)
					{
						s = Slot13;
						n = 0x0200;
					}
					else
					{
						s = Slots[ch - CPU_CMD_SAVE1].data;
						n = SLOTNUM;
					}

					// clear flash slot (address and size must be multiply of 256 B)
					Flash_Erase((u32)s + FLASH_BASE, n, 1000);

					// write program
					Flash_Program((u32)s + FLASH_BASE, (const u32*)s0, n, 1000);

					// send OK
					while (!CPU_SendReady()) {}
					CPU_Send(CPU_STATE_SYNC);
				}
				break;
			}
		}
	}
}

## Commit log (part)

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2025-09-20 v1.00

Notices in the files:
parts and their libraries:
SparkFun-Connectors: Licensing: Creative Commons ShareAlike 4.0 International - https://creativecommons.org/licenses/by-sa/4.0
